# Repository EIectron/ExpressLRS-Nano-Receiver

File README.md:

<div align="center">
  <b>
   <h1>
      ExpressLRS micro
   </h1>
   <h6>
     V1
   </h6>
  </b>

</div>

*Features*
* **Size**: 17x12mm
* **Gain**: 3.2dBi
* **Radio Efficiency**: >80%
* **Recommend Drone**: Whoop Drone
* **Range**: About 600 meters
* **Input voltage**: 5V
* **MCU**: ESP8285
* **Antenna**: Integrated SMD ceramic antenna
* **Frequency bands (Nano receiver 2.4G version)**: 2.4GHz ISM
* **Telemetry power**: 17mW
* *`DIY_2400_RX_ESP8285_SX1280_via_UART`*

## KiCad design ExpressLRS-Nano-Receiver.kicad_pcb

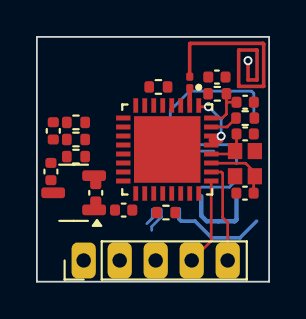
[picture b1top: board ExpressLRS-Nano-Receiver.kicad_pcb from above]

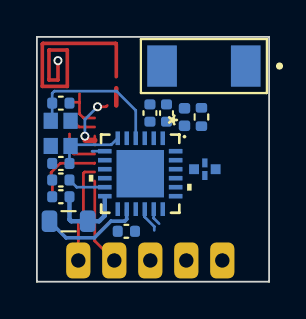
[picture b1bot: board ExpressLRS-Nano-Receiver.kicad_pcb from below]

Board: 4 copper layers, 12.9 x 13.6 mm, 34 parts (14 on the bottom side), 28 nets.

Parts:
C1: 470nF; C_0402_1005Metric
C2, C5, C10, C13: 18pF; C_0402_1005Metric
C3: 1uF; C_0402_1005Metric
C4: 4.7uF; C_0402_1005Metric
C6, C8, C17, C18: 0.1uF; C_0402_1005Metric
C11: 5.6pF; C_0201_0603Metric
C14, C15: 10nF; C_0402_1005Metric
C20, C21: 2.2uF; C_0402_1005Metric
D1: LED; LED_0402_1005Metric
E1: NN02-201; XCVR_NN02-201
FL1: 2450FM07D0034T; FIL_2450FM07D0034T
J1: Conn_01x05_Pin; PinHeader_1x05_P2.00mm_Vertical
L1: 15uH; L_0805_2012Metric
R1, R2, R3, R4, R5, R6: 12K; R_0402_1005Metric
R8: 300R; R_0402_1005Metric
R9: 1K; R_0402_1005Metric
U2: ESP8285; VQFN-32
U3: SX1280IMLTRT; QFN24_4X4_SEM
U4: AP2210N-3.3TRG1; SOT-23-3
Y1: 26MHz; Crystal_SMD_2016-4Pin_2.0x1.6mm
Y2: 52MHz; Crystal_SMD_2016-4Pin_2.0x1.6mm

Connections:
+3V3: C4.1, C6.1, C8.1, C17.1, C18.1, C21.1, R2.2, R3.2, R4.1, R6.1, R8.2, U2.1 (VDDA), U2.3 (VDD3P3), U2.4 (VDD3P3), U2.11 (VDDPST), U2.17 (VDDPST), U2.29 (VDDD), U2.30 (VDDA), U3.11 (VBAT_IO), U3.15 (VBAT), U4.2 (VOUT)
+5V: C20.2, J1.3, U4.3 (VIN)
/BTN: J1.1, R2.1, U2.15 (GPIO0)
/BUSY: U2.24 (GPIO5), U3.7 (BUSY)
/DIO1: U2.16 (GPIO4), U3.8 (DIO1)
/LED: D1.2 (A), U2.8 (XPD_DCDC)
/MISO: U2.10 (MTDI), U3.16 (MISO_TX)
/MOSI: U2.12 (MTCK), U3.17 (MOSI_RX)
/NSS: R1.2, U2.13 (MTDO), U3.19 (NSS_CTS)
/RX: J1.4, U2.25 (U0RXD)
/SCK: U2.9 (MTMS), U3.18 (SCK_RTSN)
/TX: J1.5, R8.1, U2.26 (U0TXD)
/V_DCC: C1.1, C15.2, L1.1, U3.2 (VDD_INN), U3.12 (DCC_FB)
/V_DCC2: L1.2, U3.14 (DCC_SW)
/nRST: R4.2, U2.14 (GPIO2), U3.3 (NRESET)
GND: C1.2, C2.1, C3.1, C4.2, C5.1, C6.2, C8.2, C10.2, C13.2, C14.1, C15.1, C17.2, C18.2, C20.1, C21.2, FL1.2, FL1.4, J1.2, R1.1, R5.2, R9.1, U2.33 (GND), U3.5 (GND), U3.13 (GND), U3.20 (GND), U3.21 (GND), U3.23 (GND), U3.24 (GND), U3.25 (GND), U4.1 (GND), Y1.2, Y1.4, Y2.2, Y2.4
unnamed: D1.1 (K), R9.2
unnamed: E1.1, FL1.3
unnamed: R6.2, U2.7 (CHIP_EN)
unnamed: C11.1, U2.2 (LNA)
unnamed: R5.1, U2.31 (RES12K)
unnamed: C10.1, U2.28 (XTAL_IN), Y1.1
unnamed: C13.1, U2.27 (XTAL_OUT), Y1.3
unnamed: C3.2, R3.1, U2.32 (~EXT_RST)
unnamed: FL1.1, U3.22 (RFIO)
unnamed: C14.2, U3.1 (VR_PA)
unnamed: C2.2, U3.4 (XTA), Y2.3
unnamed: C5.2, U3.6 (XTB), Y2.1

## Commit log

2024-04-21 Finished PCB
2024-05-07 updaate
